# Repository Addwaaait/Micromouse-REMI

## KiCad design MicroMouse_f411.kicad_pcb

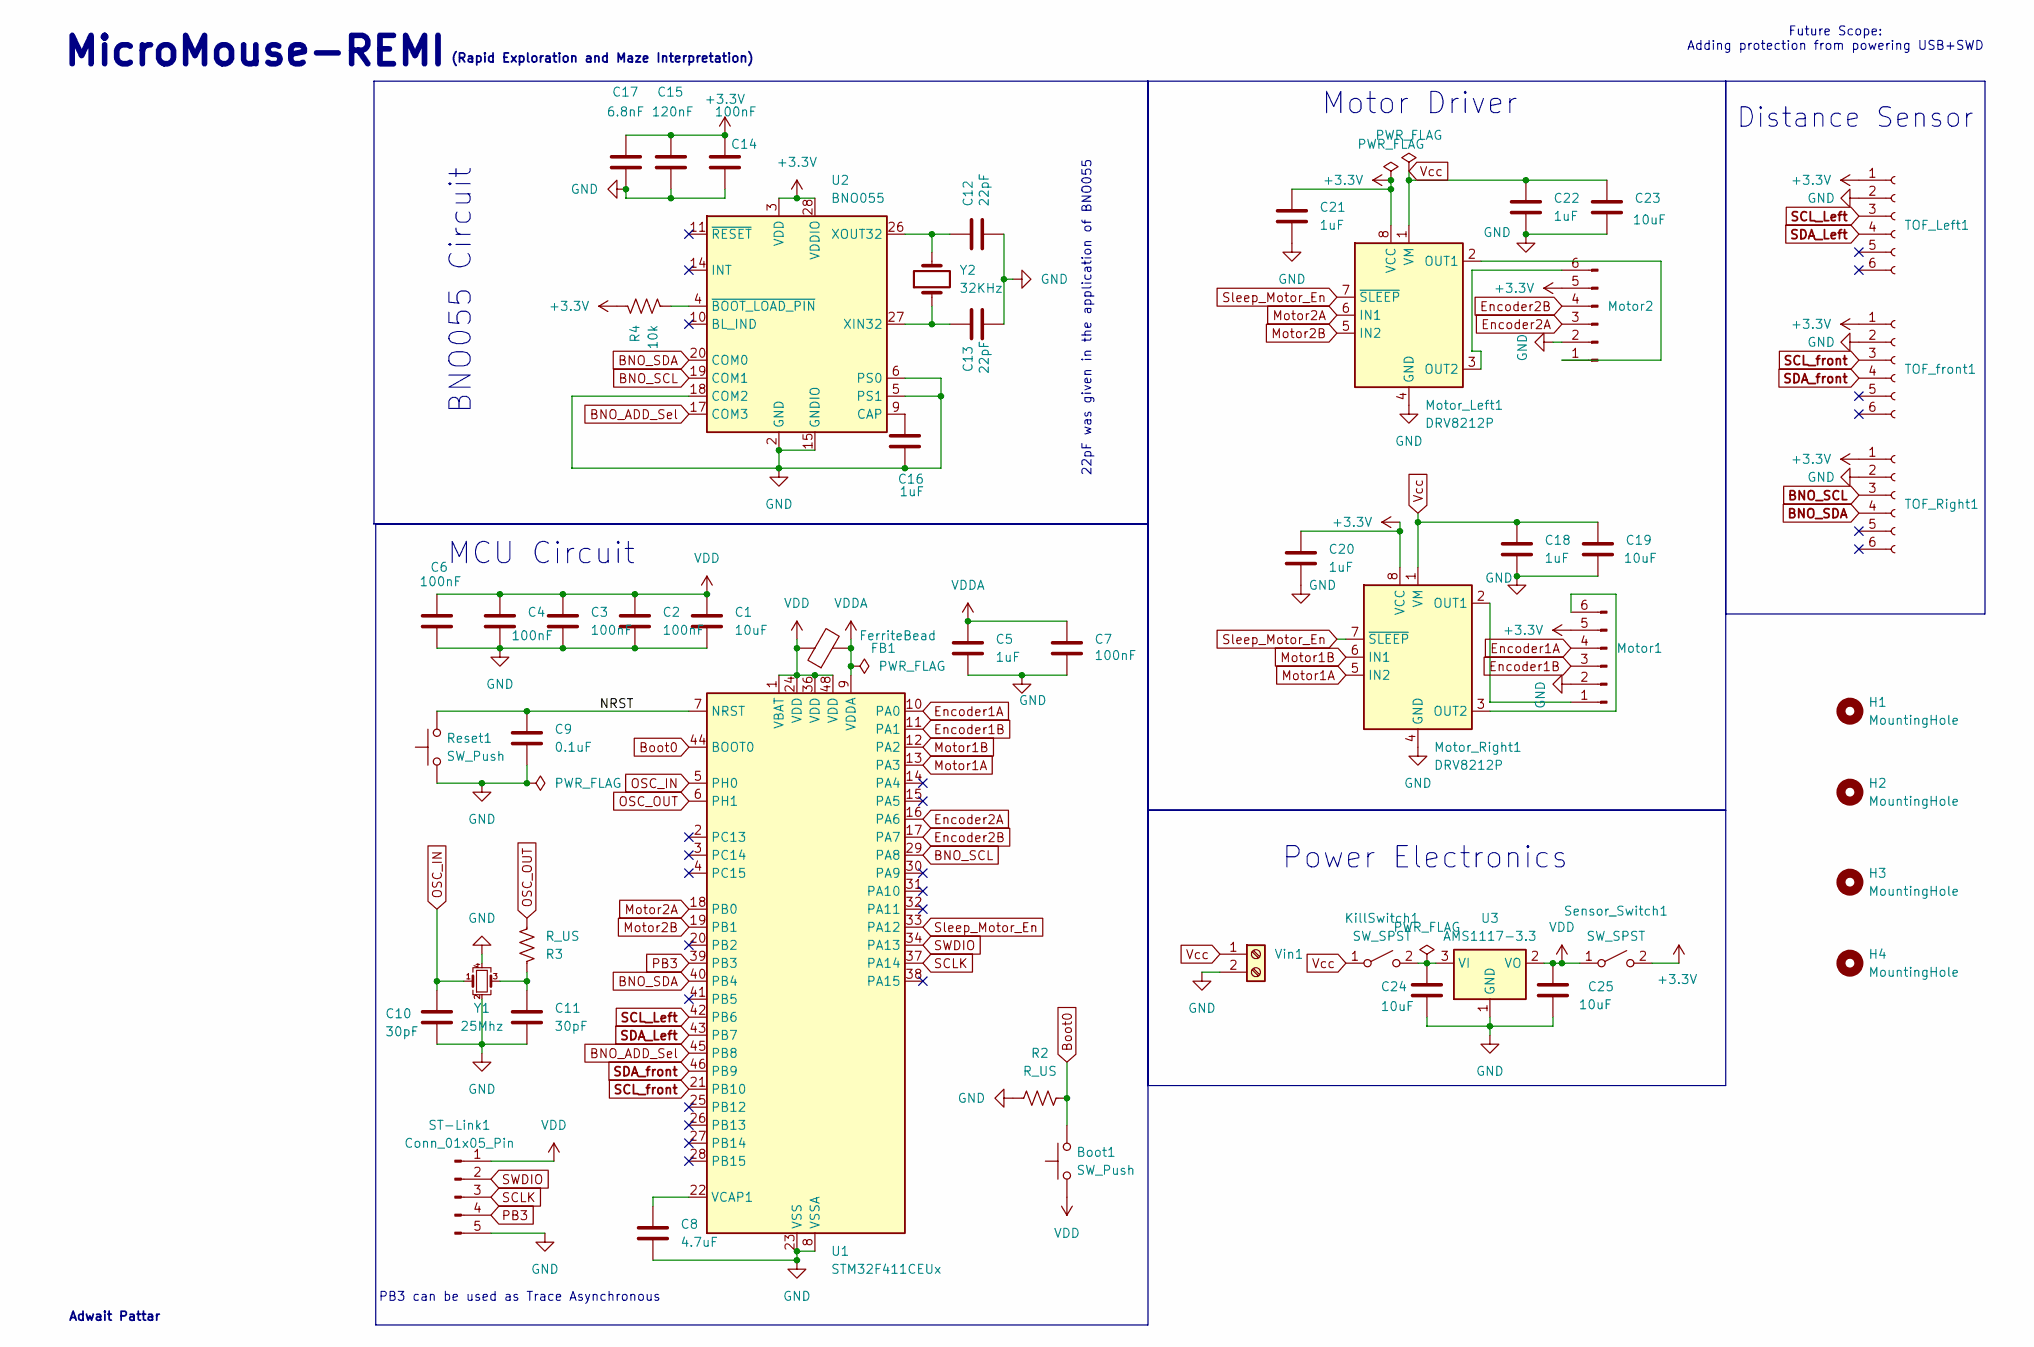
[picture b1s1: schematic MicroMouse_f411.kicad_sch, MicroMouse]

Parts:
Boot1: SW_Push; SW_Push_1P1T_NO_CK_KSC6xxJ
C1, C19, C23: 10uF; C_0603_1608Metric
C2, C3, C4, C6, C7, C14: 100nF; C_0603_1608Metric
C5, C16, C18, C20, C21, C22: 1uF; C_0603_1608Metric
C8: 4.7uF; C_0603_1608Metric
C9: 0.1uF; C_0603_1608Metric
C10, C11: 30pF; C_0805_2012Metric
C12, C13: 22pF; C_0805_2012Metric
C15: 120nF; C_0603_1608Metric
C17: 6.8nF; C_0603_1608Metric
C24, C25: 10uF; C_1206_3216Metric
FB1: FerriteBead; C_0805_2012Metric
H1, H2, H3, H4: MountingHole; MountingHole_2.2mm_M2
KillSwitch1: SW_SPST; SW_Push_1P1T_NO_CK_KSC7xxJ
Motor1, Motor2: Conn_01x06_Pin; JST_XH_S6B-XH-A-1_1x06_P2.50mm_Horizontal
Motor_Left1: DRV8212P; WSON-8-1EP_2x2mm_P0.5mm_EP0.9x1.6mm_ThermalVias
Motor_Right1: DRV8212P; WSON-8-1EP_2x2mm_P0.5mm_EP0.9x1.6mm_ThermalVias
R2, R3: R_US; R_01005_0402Metric
R4: 10k; R_01005_0402Metric
Reset1: SW_Push; SW_Push_1P1T_NO_CK_KSC6xxJ
ST-Link1: Conn_01x05_Pin; PinSocket_1x05_P2.54mm_Vertical
Sensor_Switch1: SW_SPST; SW_Push_1P1T_NO_CK_KSC7xxJ
TOF_Left1: Conn_01x06_Socket; PinHeader_1x06_P2.54mm_Vertical
TOF_Right1: Conn_01x06_Socket; PinHeader_1x06_P2.54mm_Vertical
TOF_front1: Conn_01x06_Socket; PinHeader_1x06_P2.54mm_Vertical
U1: STM32F411CEUx; QFN-48-1EP_7x7mm_P0.5mm_EP5.6x5.6mm
U2: BNO055; LGA-28_5.2x3.8mm_P0.5mm
U3: AMS1117-3.3; SOT-223-3_TabPin2
Vin1: Screw_Terminal_01x02; AMASS_XT30U-F_1x02_P5.0mm_Vertical
Y1: 25Mhz; Crystal_SMD_0603-4Pin_6.0x3.5mm
Y2: 32KHz; Crystal_SMD_3215-2Pin_3.2x1.5mm

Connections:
+3.3V: C14.2, C15.2, C17.2, C20.2, C21.2, Motor1.5, Motor2.5, Motor_Left1.8 (VCC), Motor_Right1.8 (VCC), R4.2, Sensor_Switch1.2 (B), TOF_Left1.1, TOF_Right1.1, TOF_front1.1, U2.3 (VDD), U2.28 (VDDIO)
/NRST: C9.1, Reset1.2, U1.7 (NRST)
BNO_ADD_Sel: U1.45 (PB8), U2.17 (COM3)
BNO_SCL: TOF_Right1.3, U1.29 (PA8), U2.19 (COM1)
BNO_SDA: TOF_Right1.4, U1.40 (PB4), U2.20 (COM0)
Boot0: Boot1.2, R2.2, U1.44 (BOOT0)
Encoder1A: Motor1.4, U1.10 (PA0)
Encoder1B: Motor1.3, U1.11 (PA1)
Encoder2A: Motor2.3, U1.16 (PA6)
Encoder2B: Motor2.4, U1.17 (PA7)
GND: C1.2, C2.2, C3.2, C4.2, C5.2, C6.2, C7.2, C8.2, C9.2, C10.1, C11.2, C12.2, C13.2, C14.1, C15.1, C16.2, C17.1, C18.1, C19.2, C20.1, C21.1, C22.1, C23.2, C24.2, C25.2, Motor1.2, Motor2.2, Motor_Left1.4 (GND), Motor_Left1.9 (GND), Motor_Right1.4 (GND), Motor_Right1.9 (GND), R2.1, Reset1.1, ST-Link1.5, TOF_Left1.2, TOF_Right1.2, TOF_front1.2, U1.8 (VSSA), U1.23 (VSS), U1.35 (VSS), U1.47 (VSS), U1.49 (VSS), U2.2 (GND), U2.5 (PS1), U2.6 (PS0), U2.15 (GNDIO), U2.16 (GNDIO), U2.18 (COM2), U2.25 (GNDIO), U3.1 (GND), Vin1.2, Y1.2, Y1.4
Motor1A: Motor_Right1.5 (IN2), U1.13 (PA3)
Motor1B: Motor_Right1.6 (IN1), U1.12 (PA2)
Motor2A: Motor_Left1.6 (IN1), U1.18 (PB0)
Motor2B: Motor_Left1.5 (IN2), U1.19 (PB1)
unnamed: C11.1, R3.2, Y1.3
unnamed: C24.1, KillSwitch1.2 (B), U3.3 (VI)
unnamed: Motor1.1, Motor_Right1.2 (OUT1)
unnamed: Motor1.6, Motor_Right1.3 (OUT2)
unnamed: Motor2.1, Motor_Left1.2 (OUT1)
unnamed: Motor2.6, Motor_Left1.3 (OUT2)
unnamed: C8.1, U1.22 (VCAP1)
unnamed: C16.1, U2.9 (CAP)
unnamed: C13.1, U2.27 (XIN32), Y2.1
unnamed: C12.1, U2.26 (XOUT32), Y2.2
unnamed: R4.1, U2.4 (~BOOT_LOAD_PIN)
OSC_IN: C10.2, U1.5 (PH0), Y1.1
OSC_OUT: R3.1, U1.6 (PH1)
PB3: ST-Link1.4, U1.39 (PB3)
SCLK: ST-Link1.3, U1.37 (PA14)
SCL_Left: TOF_Left1.3, U1.42 (PB6)
SCL_front: TOF_front1.3, U1.21 (PB10)
SDA_Left: TOF_Left1.4, U1.43 (PB7)
SDA_front: TOF_front1.4, U1.46 (PB9)
SWDIO: ST-Link1.2, U1.34 (PA13)
Sleep_Motor_En: Motor_Left1.7 (~SLEEP), Motor_Right1.7 (~SLEEP), U1.33 (PA12)
VDD: Boot1.1, C1.1, C2.1, C3.1, C4.1, C6.1, C25.1, FB1.1, ST-Link1.1, Sensor_Switch1.1 (A), U1.1 (VBAT), U1.24 (VDD), U1.36 (VDD), U1.48 (VDD), U3.2 (VO)
VDDA: C5.1, C7.1, FB1.2, U1.9 (VDDA)
Vcc: C18.2, C19.1, C22.2, C23.1, KillSwitch1.1 (A), Motor_Left1.1 (VM), Motor_Right1.1 (VM), Vin1.1

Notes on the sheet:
Adwait Pattar
MicroMouse-REMI
22pF was given in the application of BNO055
Motor Driver
MCU Circuit
PB3 can be used as Trace Asynchronous
(Rapid Exploration and Maze Interpretation)
BNO055 Circuit
Distance Sensor
Power Electronics
Future Scope: Adding protection from powering USB+SWD

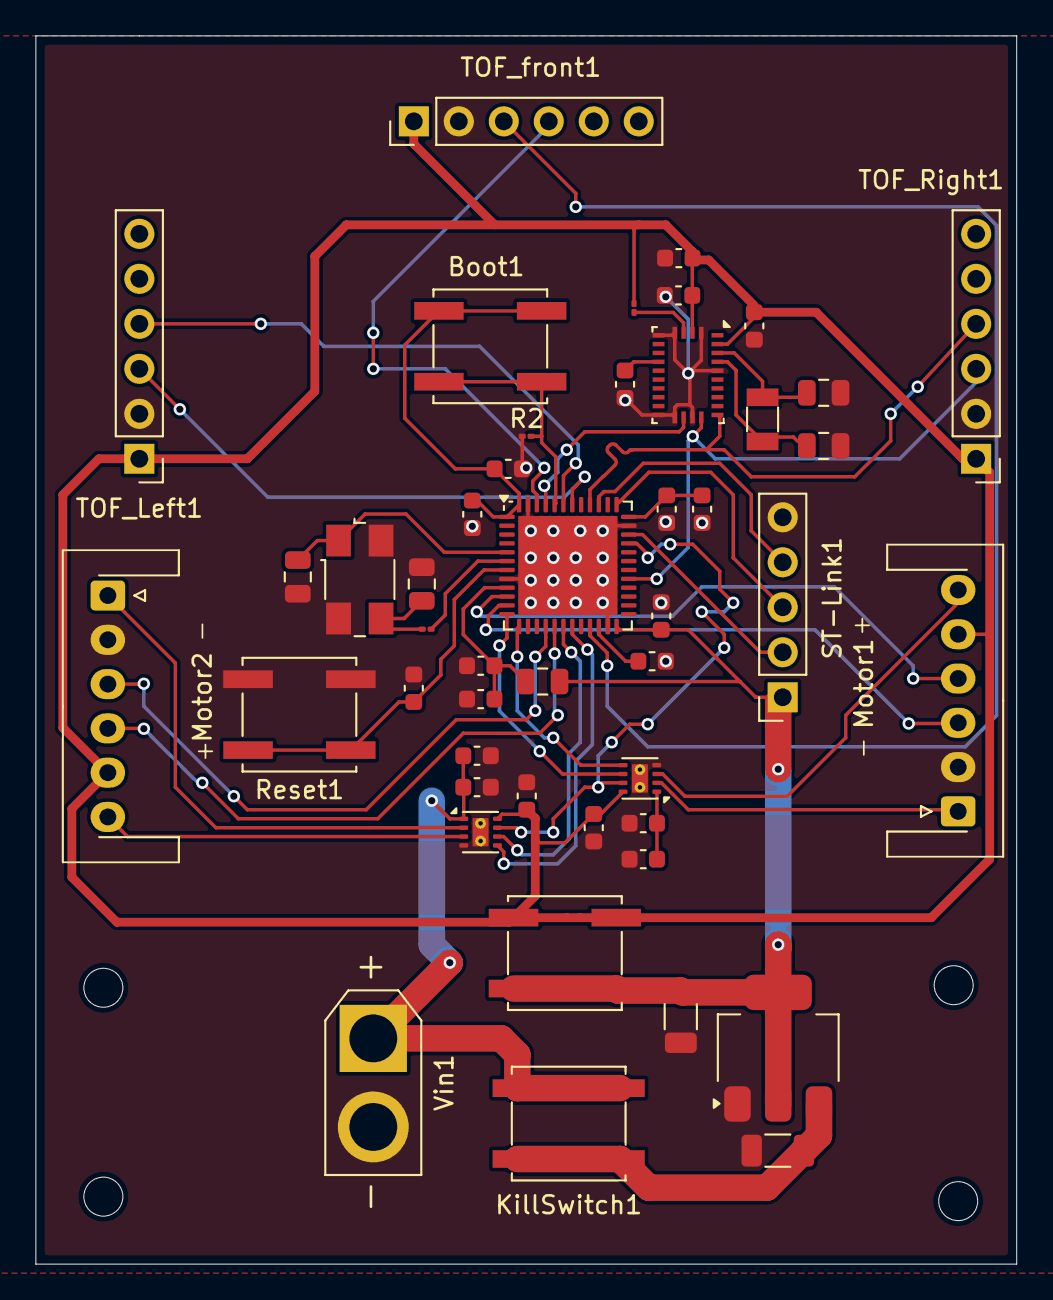
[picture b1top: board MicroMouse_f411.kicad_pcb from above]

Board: 2 copper layers, 55.4 x 69.3 mm, 51 parts (0 on the bottom side), 39 nets.

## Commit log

2025-01-19 Create LICENSE
